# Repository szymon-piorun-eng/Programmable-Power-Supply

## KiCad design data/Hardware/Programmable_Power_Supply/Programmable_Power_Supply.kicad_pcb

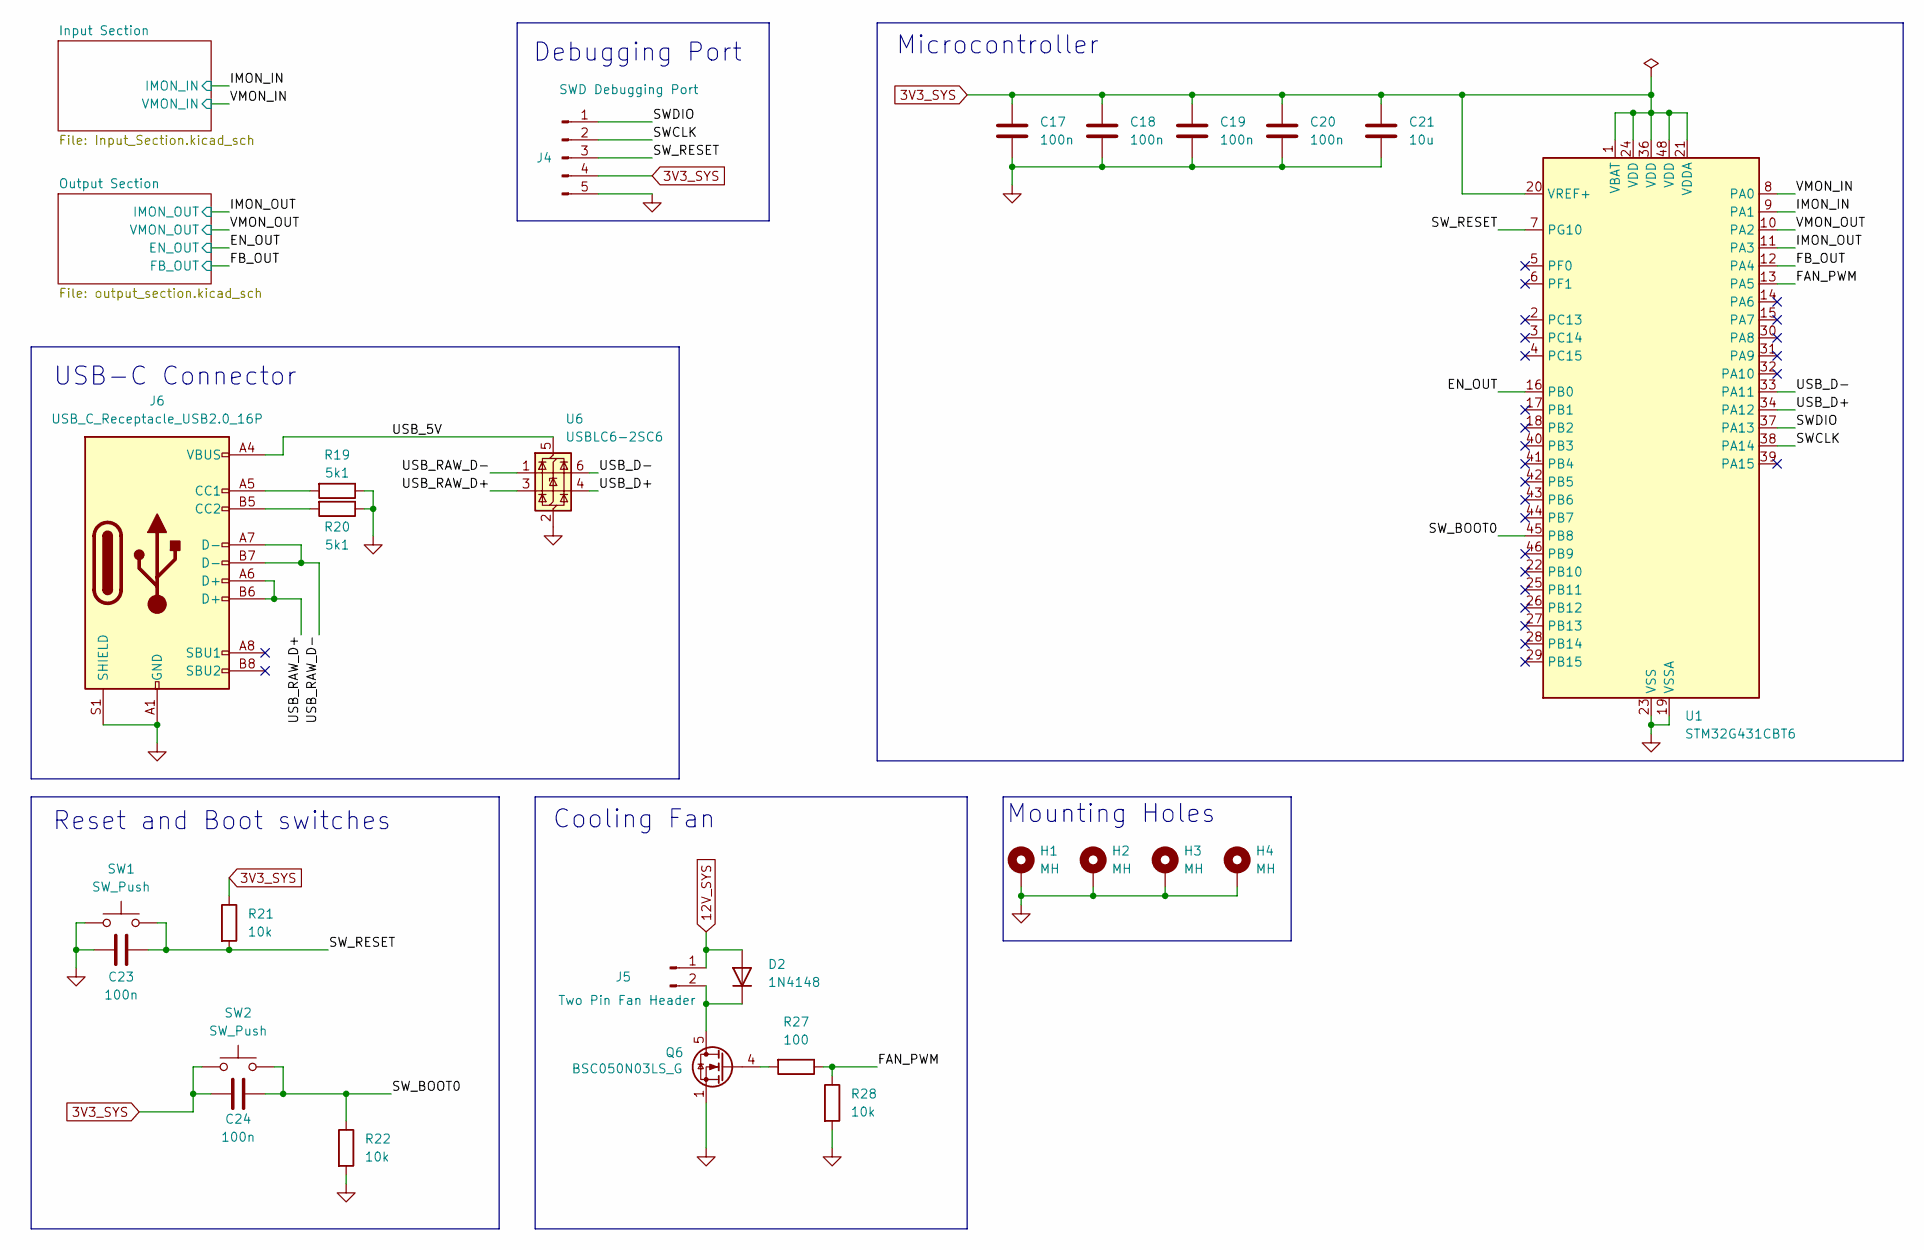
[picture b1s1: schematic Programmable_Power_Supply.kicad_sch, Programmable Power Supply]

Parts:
C17, C18, C19, C20, C23, C24: 100n; C_0201_0603Metric_Pad0.64x0.40mm_HandSolder; Mouser MLASG063SB5104KFNA01
C21: 10u; C_1206_3216Metric_Pad1.33x1.80mm_HandSolder; Mouser GXT31CR6YA106KE01L
D2: 1N4148; SOD323; Mouser 1N4148WS-HE3_A-18
H1, H2, H3, H4: MH; MountingHole_3.2mm_M3_ISO7380_Pad_TopBottom
J4: SWD Debugging Port; PinHeader_1x05_P2.54mm_Vertical
J5: Two Pin Fan Header; Molex_KK-254_AE-6410-02A_1x02_P2.54mm_Vertical; Mouser 22-23-2021
J6: USB_C_Receptacle_USB2.0_16P; USB_C_Receptacle_GCT_USB4105-xx-A_16P_TopMnt_Horizontal; Mouser USB4930-00-A
Q6: BSC050N03LS_G; Infineon_PG-TDSON-8_6.15x5.15mm
R19, R20: 5k1; R_0603_1608Metric_Pad0.98x0.95mm_HandSolder; Mouser CR0603-FX-5101ELF
R21, R22, R28: 10k; R_0603_1608Metric_Pad0.98x0.95mm_HandSolder; Mouser RCA060310K0FKEC
R27: 100; R_0603_1608Metric_Pad0.98x0.95mm_HandSolder; Mouser RT0603BRB07100RL
SW1, SW2: SW_Push; TS046650BK100SMTTR; Mouser TS04-66-50-BK-100-SMT-TR
U1: STM32G431CBT6; LQFP-48_7x7mm_P0.5mm; Mouser STM32G431CBT6
U6: USBLC6-2SC6; SOT-23-6; Mouser USBLC6-2SC6

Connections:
3V3_SYS: C17.1, C18.1, C19.1, C20.1, C21.1, C24.2, J4.4, R21.1, SW2.1, U1.1 (VBAT), U1.20 (VREF+), U1.21 (VDDA), U1.24 (VDD), U1.36 (VDD), U1.48 (VDD); also elsewhere on the board
12V_SYS: D2.2 (A), J5.1; also elsewhere on the board
/EN_OUT: U1.16 (PB0); also elsewhere on the board
/FAN_PWM: R27.1, R28.1, U1.13 (PA5)
/FB_OUT: U1.12 (PA4); also elsewhere on the board
/IMON_IN: U1.9 (PA1); also elsewhere on the board
/IMON_OUT: U1.11 (PA3); also elsewhere on the board
/SWCLK: J4.2, U1.38 (PA14)
/SWDIO: J4.1, U1.37 (PA13)
/SW_BOOT0: C24.1, R22.1, SW2.2, U1.45 (PB8)
/SW_RESET: C23.2, J4.3, R21.2, SW1.2, U1.7 (PG10)
/USB_5V: J6.A4 (VBUS), J6.A9 (VBUS), J6.B4 (VBUS), J6.B9 (VBUS), U6.5 (VBUS)
/USB_D+: U1.34 (PA12), U6.4 (I/O2)
/USB_D-: U1.33 (PA11), U6.6 (I/O1)
/USB_RAW_D+: J6.A6 (D+), J6.B6 (D+), U6.3 (I/O2)
/USB_RAW_D-: J6.A7 (D-), J6.B7 (D-), U6.1 (I/O1)
/VMON_IN: U1.8 (PA0); also elsewhere on the board
/VMON_OUT: U1.10 (PA2); also elsewhere on the board
GND: C17.2, C18.2, C19.2, C20.2, C21.2, C23.1, H1.1, H2.1, H3.1, H4.1, J4.5, J6.A1 (GND), J6.A12 (GND), J6.B1 (GND), J6.B12 (GND), J6.S1 (SHIELD), Q6.1 (S), Q6.2 (S), Q6.3 (S), R19.1, R20.1, R22.2, R28.2, SW1.1, U1.19 (VSSA), U1.23 (VSS), U1.35 (VSS), U1.47 (VSS), U6.2 (GND); also elsewhere on the board
unnamed: D2.1 (K), J5.2, Q6.5 (D)
unnamed: J6.A5 (CC1), R19.2
unnamed: J6.B5 (CC2), R20.2
unnamed: Q6.4 (G), R27.2

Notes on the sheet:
Microcontroller
Mounting Holes
Debugging Port
USB-C Connector
Reset and Boot switches
Cooling Fan

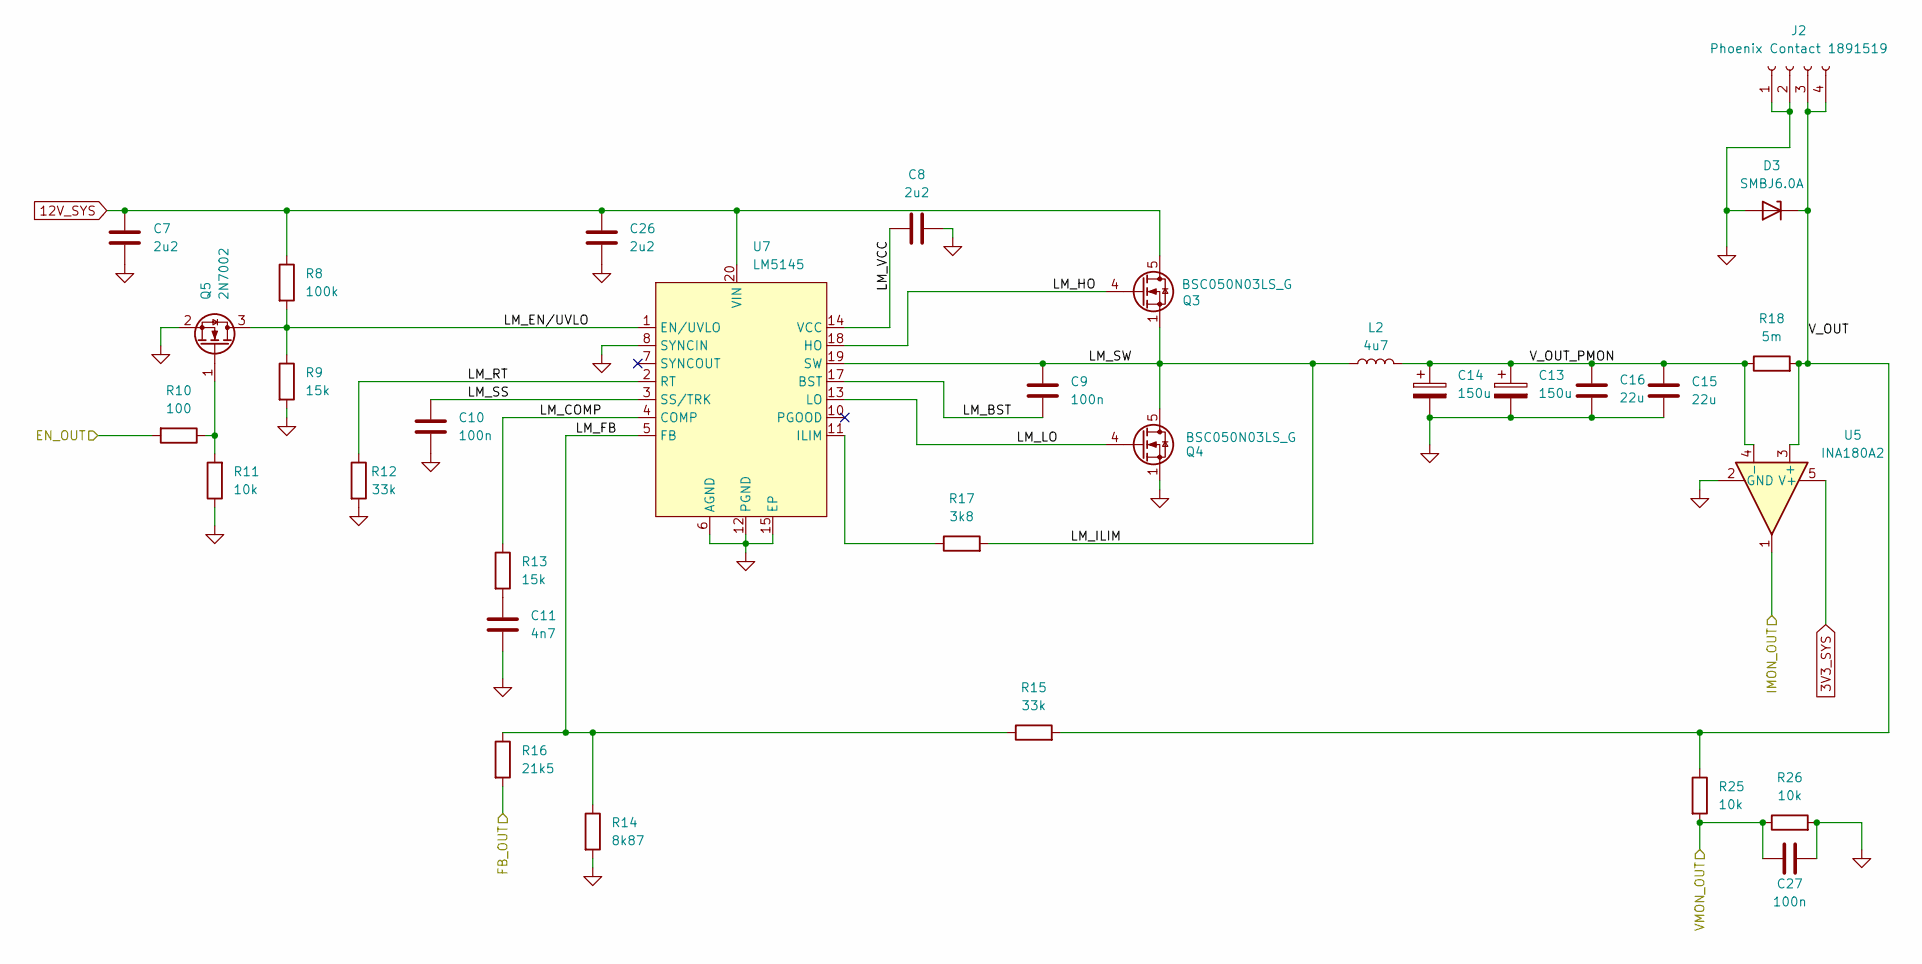
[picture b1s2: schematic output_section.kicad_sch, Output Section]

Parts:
C7, C8, C26: 2u2; C_1206_3216Metric_Pad1.33x1.80mm_HandSolder; Mouser 885382208016
C9, C10, C27: 100n; C_0201_0603Metric_Pad0.64x0.40mm_HandSolder; Mouser MLASG063SB5104KFNA01
C11: 4n7; C_0805_2012Metric_Pad1.18x1.45mm_HandSolder; Mouser KAM21BR72A472KT
C13, C14: 150u; CAPPM7343X310N; Mouser 593D157X0010D2TE3
C15, C16: 22u; C_1206_3216Metric_Pad1.33x1.80mm_HandSolder; Mouser GRM31CC71C226ME11K
D3: SMBJ6.0A; D_SMB_Handsoldering; Mouser SMBJ6.0A
J2: Phoenix Contact 1891519; 2 pin power connector; Mouser 1891519
L2: 4u7; L_Wuerth_HCI-1365; Mouser 7443551470
Q3, Q4: BSC050N03LS_G; Infineon_PG-TDSON-8_6.15x5.15mm
Q5: 2N7002; SOT-23; Mouser 2N7002
R8: 100k; R_0603_1608Metric_Pad0.98x0.95mm_HandSolder; Mouser RCA0603100KFKEC
R9, R13: 15k; R_0603_1608Metric_Pad0.98x0.95mm_HandSolder; Mouser MCT06030C1502FPW00
R10: 100; R_0603_1608Metric_Pad0.98x0.95mm_HandSolder; Mouser RT0603BRB07100RL
R11, R25, R26: 10k; R_0603_1608Metric_Pad0.98x0.95mm_HandSolder; Mouser RCA060310K0FKEC
R12, R15: 33k; R_0603_1608Metric_Pad0.98x0.95mm_HandSolder; Mouser RCA060333K0FKEA
R14: 8k87; R_0603_1608Metric_Pad0.98x0.95mm_HandSolder; Mouser 560112116137
R16: 21k5; R_0603_1608Metric_Pad0.98x0.95mm_HandSolder; Mouser CRT0603-FZ-2152ELF
R17: 3k8; R_0603_1608Metric_Pad0.98x0.95mm_HandSolder; Mouser RN73R1JTTD3282F100
R18: 5m; R_2512_6332Metric_Pad1.40x3.35mm_HandSolder; Mouser WSLP25125L000FEA
U5: INA180A2; SOT-23-5; Mouser INA180A2IDBVR
U7: LM5145; RGY0020B; Mouser LM5145RGYR

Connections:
3V3_SYS: U5.5 (V+); also elsewhere on the board
12V_SYS: C7.2, C26.2, Q3.5 (D), R8.1, U7.20 (VIN); also elsewhere on the board
/EN_OUT: R10.2; also elsewhere on the board
/FB_OUT: R16.2; also elsewhere on the board
/IMON_OUT: U5.1; also elsewhere on the board
/Output Section/LM_BST: C9.2, U7.17 (BST)
/Output Section/LM_COMP: R13.1, U7.4 (COMP)
/Output Section/LM_EN/UVLO: Q5.3 (D), R8.2, R9.1, U7.1 (EN/UVLO)
/Output Section/LM_FB: R14.1, R15.1, R16.1, U7.5 (FB)
/Output Section/LM_HO: Q3.4 (G), U7.18 (HO)
/Output Section/LM_ILIM: C9.1, L2.1, Q3.1 (S), Q3.2 (S), Q3.3 (S), Q4.5 (D), R17.2, U7.19 (SW)
/Output Section/LM_LO: Q4.4 (G), U7.13 (LO)
/Output Section/LM_RT: R12.1, U7.2 (RT)
/Output Section/LM_SS: C10.1, U7.3 (SS/TRK)
/Output Section/LM_VCC: C8.1, U7.14 (VCC)
/Output Section/V_OUT: D3.1 (K), J2.3, J2.4, R15.2, R18.2, R25.1, U5.3 (+)
/Output Section/V_OUT_PMON: C13.1, C14.1, C15.1, C16.1, L2.2, R18.1, U5.4 (-)
/VMON_OUT: C27.1, R25.2, R26.1; also elsewhere on the board
GND: C7.1, C8.2, C10.2, C11.2, C13.2, C14.2, C15.2, C16.2, C26.1, C27.2, D3.2 (A), J2.1, J2.2, Q4.1 (S), Q4.2 (S), Q4.3 (S), Q5.2 (S), R9.2, R11.1, R12.2, R14.2, R26.2, U5.2 (GND), U7.6 (AGND), U7.8 (SYNCIN), U7.12 (PGND), U7.15 (EP), U7.V; also elsewhere on the board
unnamed: C11.1, R13.2
unnamed: Q5.1 (G), R10.1, R11.2
unnamed: R17.1, U7.11 (ILIM)

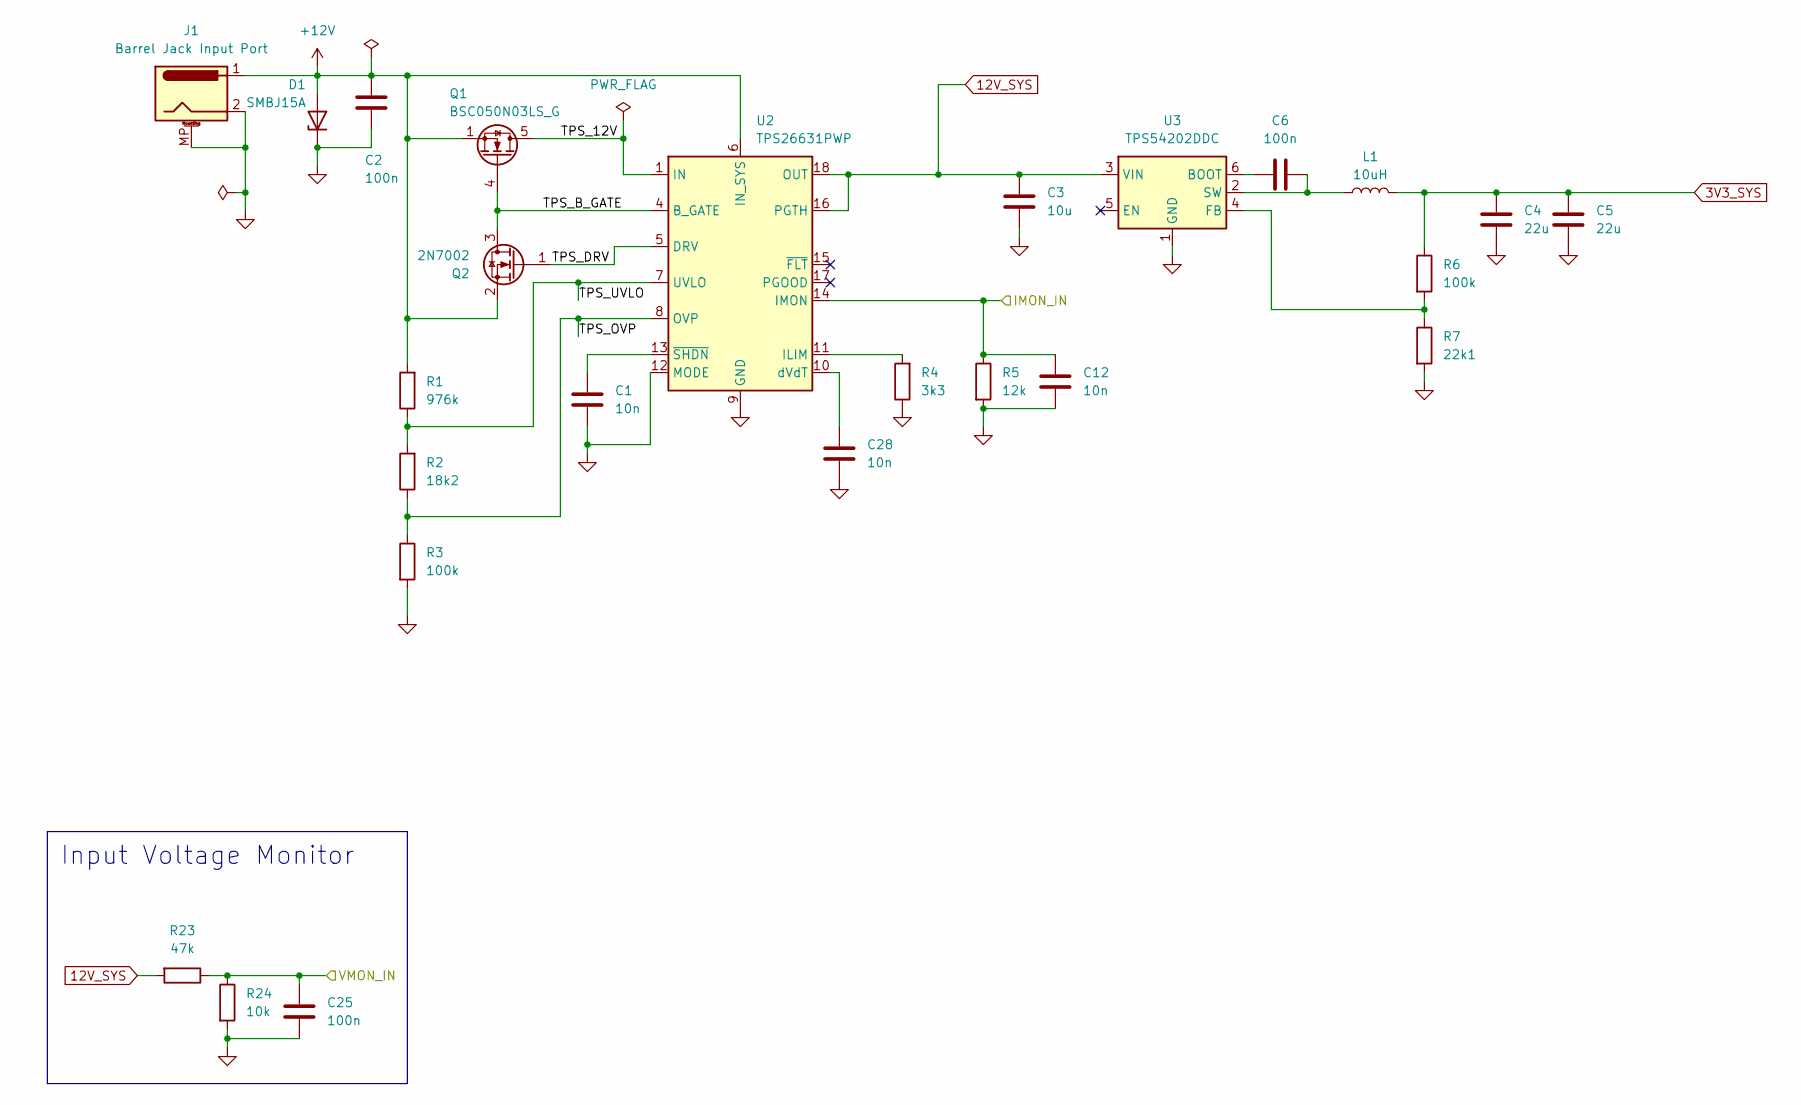
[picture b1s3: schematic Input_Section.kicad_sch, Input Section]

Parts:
C1, C12, C28: 10n; C_0201_0603Metric_Pad0.64x0.40mm_HandSolder; Mouser MLASU063SB5103KFNA01
C2, C6, C25: 100n; C_0201_0603Metric_Pad0.64x0.40mm_HandSolder; Mouser MLASG063SB5104KFNA01
C3: 10u; C_1206_3216Metric_Pad1.33x1.80mm_HandSolder; Mouser GXT31CR6YA106KE01L
C4, C5: 22u; C_1206_3216Metric_Pad1.33x1.80mm_HandSolder; Mouser GRM31CC71C226ME11K
D1: SMBJ15A; D_SMB_Handsoldering; Mouser SMBJ15A
J1: Barrel Jack Input Port; BarrelJack_CUI_PJ-063AH_Horizontal; Mouser PJ-063AH
L1: 10uH; SRP6540; Mouser SRP6540-100M
Q1: BSC050N03LS_G; Infineon_PG-TDSON-8_6.15x5.15mm
Q2: 2N7002; SOT-23; Mouser 2N7002
R1: 976k; R_0603_1608Metric_Pad0.98x0.95mm_HandSolder; Mouser CRCW0603976KFKTA
R2: 18k2; R_0603_1608Metric_Pad0.98x0.95mm_HandSolder; Mouser AF0603FR-0718K2L
R3, R6: 100k; R_0603_1608Metric_Pad0.98x0.95mm_HandSolder; Mouser RCA0603100KFKEC
R4: 3k3; R_0603_1608Metric_Pad0.98x0.95mm_HandSolder; Mouser CR0603-FX-3301ELF
R5: 12k; R_0603_1608Metric_Pad0.98x0.95mm_HandSolder; Mouser 560112116040
R7: 22k1; R_0603_1608Metric_Pad0.98x0.95mm_HandSolder; Mouser CRCW060322K1FKEBC
R23: 47k; R_0603_1608Metric_Pad0.98x0.95mm_HandSolder; Mouser CRCW060347K0FKECC
R24: 10k; R_0603_1608Metric_Pad0.98x0.95mm_HandSolder; Mouser RCA060310K0FKEC
U2: TPS26631PWP; HTSSOP-20-1EP_4.4x6.5mm_P0.65mm_EP3.4x6.5mm_Mask2.96x2.96mm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; Mouser TPS26633PWPR
U3: TPS54202DDC; SOT-23-6; Mouser TPS542025DDCR

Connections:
3V3_SYS: C4.1, C5.1, L1.2, R6.1; also elsewhere on the board
12V_SYS: C3.1, R23.2, U2.16 (PGTH), U2.18 (OUT), U2.19 (OUT), U2.20 (OUT), U3.3 (VIN); also elsewhere on the board
+12V: C2.1, D1.2 (A), J1.1, Q1.1 (S), Q1.2 (S), Q1.3 (S), Q2.2 (S), R1.2, U2.6 (IN_SYS)
/IMON_IN: C12.1, R5.1, U2.14 (IMON); also elsewhere on the board
/Input Section/TPS_12V: Q1.5 (D), U2.1 (IN), U2.2 (IN), U2.3 (IN)
/Input Section/TPS_B_GATE: Q1.4 (G), Q2.3 (D), U2.4 (B_GATE)
/Input Section/TPS_DRV: Q2.1 (G), U2.5 (DRV)
/Input Section/TPS_OVP: R2.1, R3.1, U2.8 (OVP)
/Input Section/TPS_UVLO: R1.1, R2.2, U2.7 (UVLO)
/VMON_IN: C25.1, R23.1, R24.1; also elsewhere on the board
GND: C1.2, C2.2, C3.2, C4.2, C5.2, C12.2, C25.2, C28.2, D1.1 (K), J1.2, J1.MP (MountPin), R3.2, R4.1, R5.2, R7.2, R24.2, U2.9 (GND), U2.12 (MODE), U2.21 (GND), U3.1 (GND); also elsewhere on the board
unnamed: R4.2, U2.11 (ILIM)
unnamed: C28.1, U2.10 (dVdT)
unnamed: C1.1, U2.13 (~SHDN)
unnamed: C6.1, U3.6 (BOOT)
unnamed: R6.2, R7.1, U3.4 (FB)
unnamed: C6.2, L1.1, U3.2 (SW)

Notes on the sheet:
Input Voltage Monitor

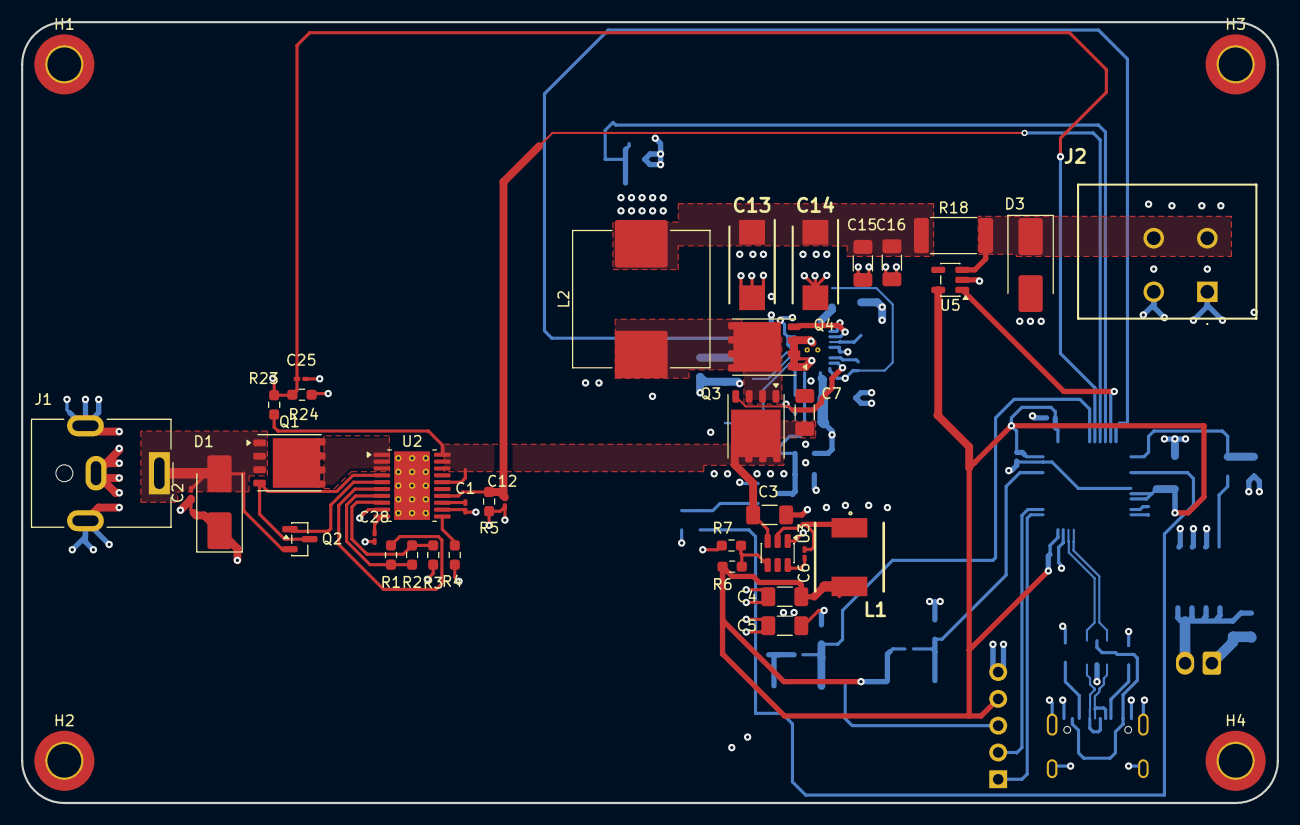
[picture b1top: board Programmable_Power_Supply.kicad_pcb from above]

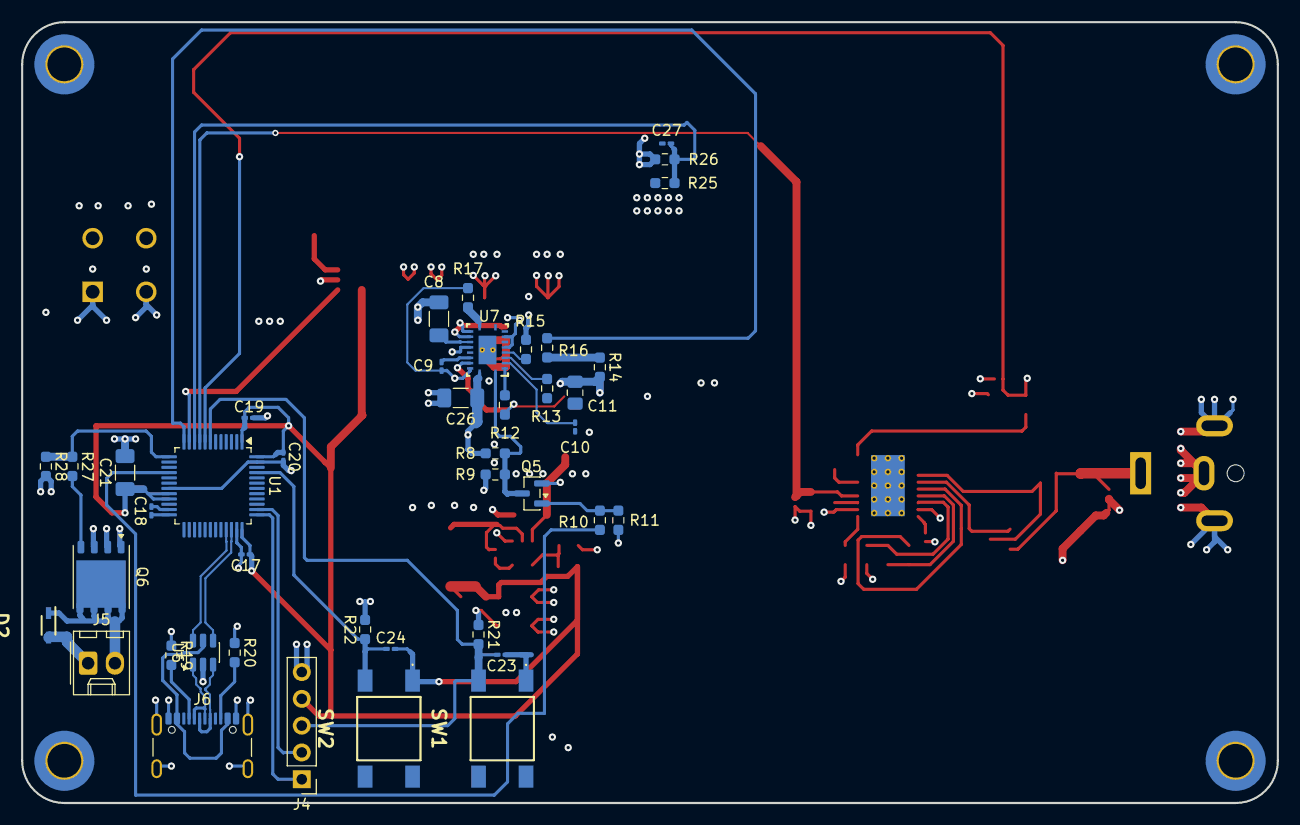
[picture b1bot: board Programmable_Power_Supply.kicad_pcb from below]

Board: 4 copper layers, 119.0 x 74.0 mm, 83 parts (42 on the bottom side), 50 nets.

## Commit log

2026-03-15 chore: Adding git ignore to project dir.
2026-03-15 chore: Adding text QA tools.
2026-03-15 docs: Adding data source for SRS and tests.
2026-03-15 docs: Adding scripts for documentation automation.
2026-03-15 chore: Adding basic mkdocs configuration.
2026-03-15 docs: Adding CI for github pages and docs QA.
2026-03-15 docs: Creating SRS file.
2026-03-24 docs: Modifying linters for current project.
2026-03-24 docs: Developing SRS (3 new chaps)
2026-04-01 docs: Adding risk SSOT.
2026-04-01 docs: Updating spell-checker.
2026-04-01 docs: Adding tests SSOT.
2026-04-01 docs: Adding risk analysis page.
2026-04-01 docs: Adding summary to each section.
2026-04-01 docs: Adding new files to mkdocs watchlist.
2026-04-01 docs: Adding new macro for rendering risk tables.
2026-04-02 docs: Adding more risk to risk SSOT
2026-04-02 docs: Updating risk analysis with new identified risks
2026-04-04 Deployed 21f0dc1 with MkDocs version: 1.6.1
2026-04-08 docs: Editing gitignore for KiCad temporary files
2026-04-08 docs: Adding initial electrical diagram with input section implemented
2026-04-08 docs: Updating git ignore to ignore KiCad auto back-ups
2026-04-09 feat: Adding output section to the schematic.
2026-04-09 feat: First draw of full schematic with all footprints and symbols.
2026-04-10 feat: Final version of revision A of the schematic with mouser product numbers attached.
2026-04-16 feat: First full layout of the PCB
2026-04-16 feat: Layout of USB-C port and final beta version of the board.
